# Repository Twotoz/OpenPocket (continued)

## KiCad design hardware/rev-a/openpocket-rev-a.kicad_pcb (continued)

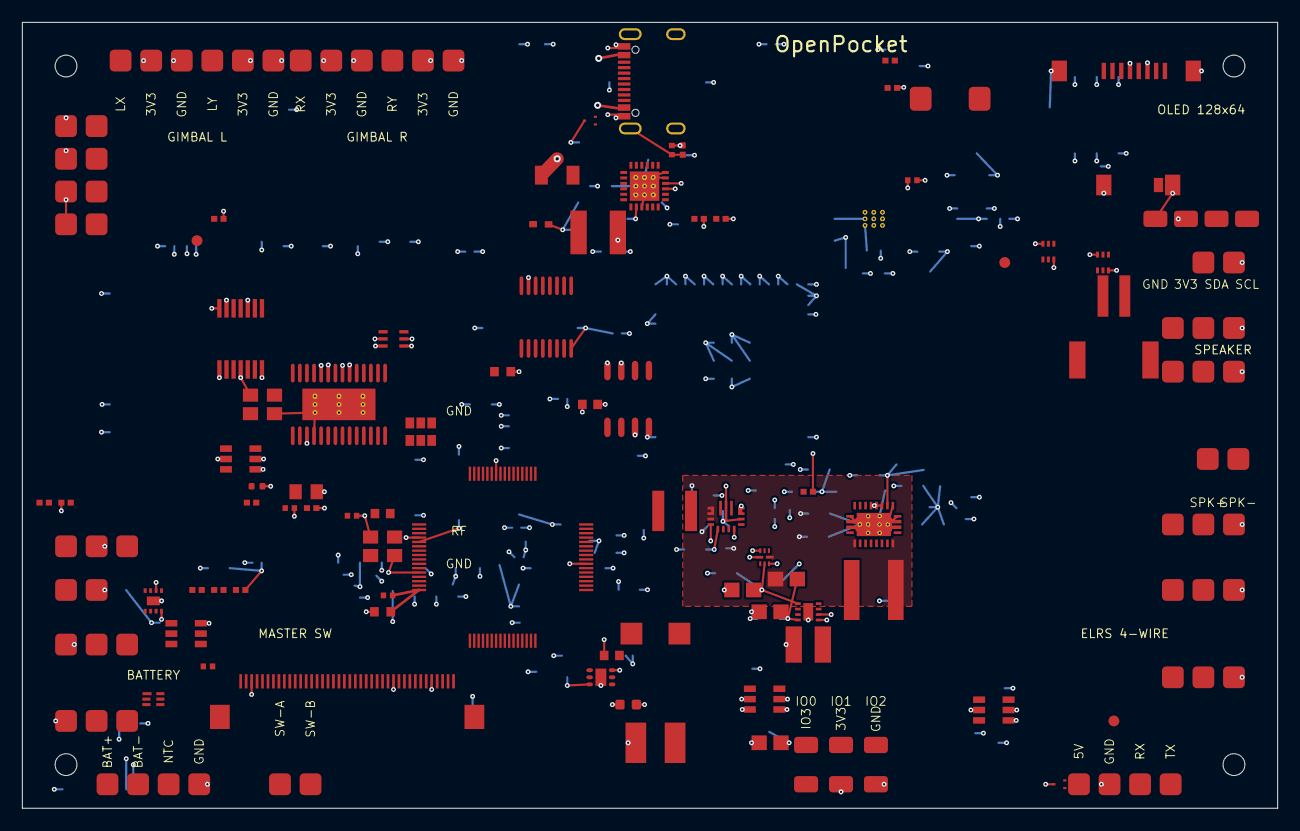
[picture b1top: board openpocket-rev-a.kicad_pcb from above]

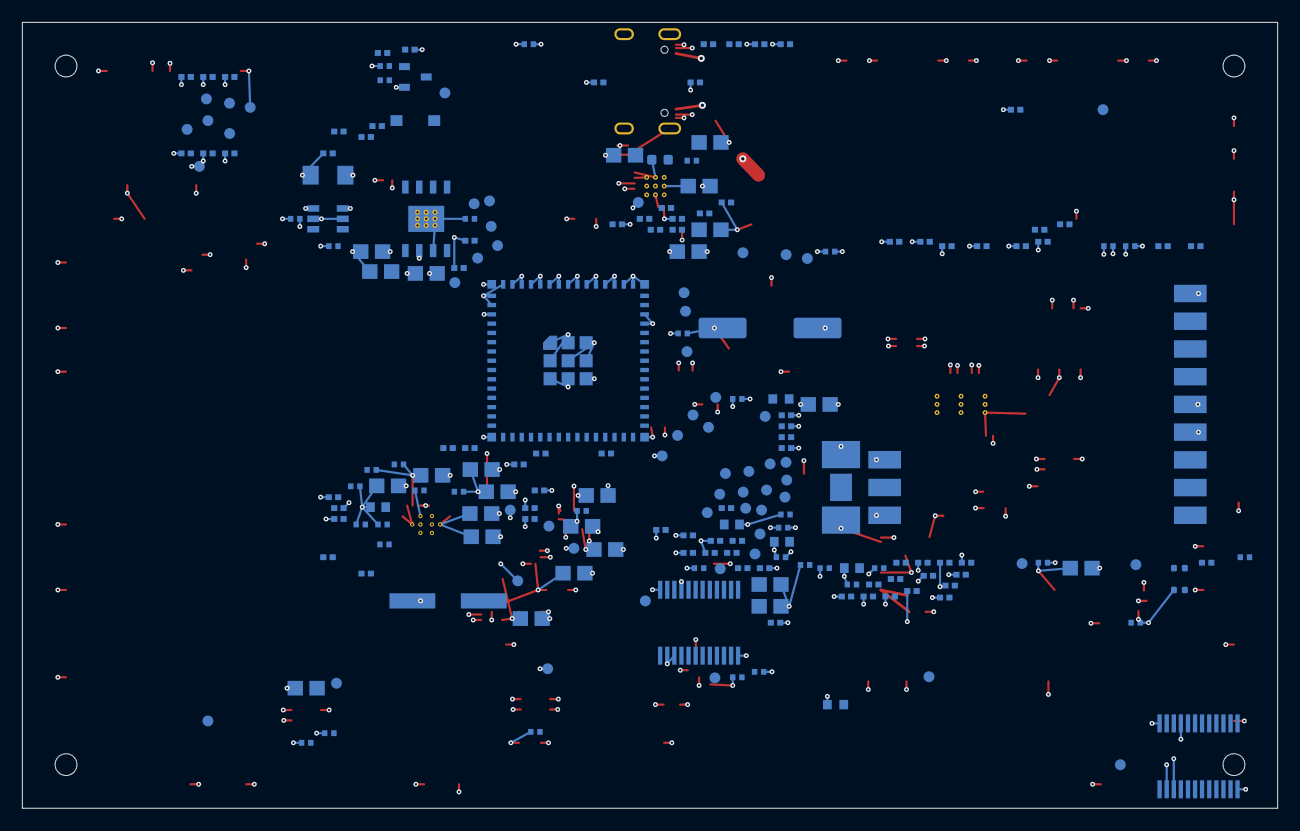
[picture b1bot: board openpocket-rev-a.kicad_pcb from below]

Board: 8 copper layers, 115.0 x 72.0 mm, 315 parts (220 on the bottom side), 235 nets.

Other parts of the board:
FID1, FID2, FID3, FID4, FID5, FID6: Fiducial_1mm_Mask2mm
MH1, MH2, MH3, MH4: MountingHole_2mm

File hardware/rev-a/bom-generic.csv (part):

Designator,Value,Manufacturer,MPN,LCSC,Package,Qty,DNP,Notes
U1,ESP32-S3-MINI-1U-N8,Espressif,ESP32-S3-MINI-1U-N8,C2980299,ESP32-S3-MINI-1U,1,no,
J2,USB-C,GCT,USB4105-GF-A,C3020560,USB4105-GF-A,1,no,
ESD1,USB ESD,Texas Instruments,TPD2EUSB30DRTR,C97502,SOT-9X3-3,1,no,
F1,USB VBUS resettable fuse,Littelfuse,1206L200PR,C151163,1206,1,no,
TVS1,USB VBUS TVS,onsemi,ESD5Z5.0T1G,C82044,SOD-523,1,no,
U2,1S charger/power path,Texas Instruments,BQ25895RTWR,C80200,WQFN-24-EP,1,no,
U3,1S protector,Texas Instruments,BQ29700DSER,C183096,WSON-6,1,no,
Q1,dual protection FET,FUXINSEMI,FS8205A,C908265,SOT-23-6,1,no,
U4,fuel gauge,Analog Devices,MAX17048G+T10,C2682616,TDFN-8-EP,1,no,
U20,master load switch,Texas Instruments,TPS22992SRXNR,C3229354,WQFN-8,1,no,
U5,3V3 buck-boost,Texas Instruments,TPS63070RNMR,C109322,VQFN-15,1,no,
U6,5V boost,Texas Instruments,TPS61088RHLR,C87357,VQFN-20-EP,1,no,
U7,5V_VIDEO load switch,Texas Instruments,TPS22918DBVR,C131941,SOT-23-6,1,no,
U8,5V_DISPLAY load switch,Texas Instruments,TPS22918DBVR,C131941,SOT-23-6,1,no,
U9,5V_ELRS load switch,Texas Instruments,TPS22918DBVR,C131941,SOT-23-6,1,no,
U10,display 3V3 buck,Texas Instruments,TPS62162DSGR,C40256,WSON-8-EP,1,no,
MOD1,RX5808 SPI receiver,WREKD,RX5808 SPI-modified,C2908157,SMD-12_23.0X28.0X2.54P,1,no,pre-order or consigned
U11,analog OSD,Zhongkewei,AT7456E,C82351,TSSOP-28-EP,1,no,
U12,OSD 3V3-to-5V,Texas Instruments,SN74AHCT125PWR,C36365,TSSOP-14,1,no,
U13,OSD 5V-to-3V3,Texas Instruments,SN74LVC1T45DCKR,C9382,SC70-6,1,no,
U14,CVBS TFT controller,Actions Microelectronics,AMT630A,C9900018923,LQFP-64_14x14_P0.4,1,no,
U15,AMT boot flash,Winbond,W25X05CLSNIG,C2641187,SOIC-8,1,no,
U16,AMT flash mux,Texas Instruments,SN74CB3Q3257PWR,C397142,TSSOP-16,1,no,
J1,ER-TFT050A3-2 FFC,Hirose,FH12-40S-0.5SH(55),C202114,FH12-40S-0.5SH(55),1,no,
U17,backlight boost,Texas Instruments,TPS61165DRVR,C122568,WSON-6-EP,1,no,
U18,GPIO expander 0x20,Texas Instruments,TCA9535PWR,C130204,TSSOP-24,1,no,
U19,GPIO expander 0x21,Texas Instruments,TCA9535PWR,C130204,TSSOP-24,1,no,
BZ1,passive magnetic buzzer,Fengming,YS-SBZ7525C05R30,C7421675,SMD-7.5x7.5,1,no,
Q2,Q_BUZZ buzzer MOSFET,Alpha & Omega,AO3400A,C20917,SOT-23,1,no,
D2,D_BUZZ buzzer flyback,LGE,1N4148W,C81598,SOD-123,1,no,
U21,I2S speaker amplifier,Nsiway,NS4168,C910588,ESOP-8-EP,1,no,
J4,speaker connector,JST,S2B-PH-SM4-TB(LF)(SN),C295747,JST-PH-2-SMD,1,no,
J13,speaker solder pads,OpenPocket,SOLDER-PADS-2,CONS,EDGE-PADS-2,1,yes,integral differential speaker pads; neither pad is ground
J14,SSD1306 128x64 OLED pads,OpenPocket,DEV-PADS-4,CONS,DEV-PADS-4,1,yes,four-wire SSD1306/SH1106 128x64 OLED; shared GPIO15/GPIO16 I2C bus
J15,expander developer pads,OpenPocket,DEV-PADS-6,CONS,DEV-PADS-6,1,yes,hand-solder TCA9535 U19 slow-I/O access
U22,3V3_SD load switch,Texas Instruments,TPS22918DBVR,C131941,SOT-23-6,1,no,
J12,push-push microSD,SOFNG,TF-001A-P3,C3021282,TF-001A-P3,1,no,card detect active-low; card ejects toward top edge
ESD2,microSD ESD array A,Texas Instruments,TPD4E001DRLR,C527516,SOT-563,1,no,
ESD3,microSD ESD array B,Texas Instruments,TPD4E001DRLR,C527516,SOT-563,1,no,
TP1,3V3_SD test pad,OpenPocket,PCB-TEST-PAD-1.0MM,N/A,TEST-PAD-1.0MM,1,yes,bare ENIG copper test feature; not an assembled component
TP2,SD_CLK test pad,OpenPocket,PCB-TEST-PAD-1.0MM,N/A,TEST-PAD-1.0MM,1,yes,bare ENIG copper test feature; not an assembled component
TP3,SD_CMD test pad,OpenPocket,PCB-TEST-PAD-1.0MM,N/A,TEST-PAD-1.0MM,1,yes,bare ENIG copper test feature; not an assembled component
TP4,SD_D0 test pad,OpenPocket,PCB-TEST-PAD-1.0MM,N/A,TEST-PAD-1.0MM,1,yes,bare ENIG copper test feature; not an assembled component
TP5,SD_CARD_DETECT test pad,OpenPocket,PCB-TEST-PAD-1.0MM,N/A,TEST-PAD-1.0MM,1,yes,bare ENIG copper test feature; not an assembled component
TP6,GND test pad,OpenPocket,PCB-TEST-PAD-1.0MM,N/A,TEST-PAD-1.0MM,1,yes,bare ENIG copper test feature; not an assembled component
J3,battery/NTC,OpenPocket,SOLDER-PADS-4,CONS,EDGE-PADS-4,1,yes,"integral solder pads; user-wired, not an assembly item"
J5,master switch,OpenPocket,SOLDER-PADS-2,CONS,EDGE-PADS-2,1,yes,"integral solder pads; user-wired, not an assembly item"
J6,ELRS,OpenPocket,SOLDER-PADS-4,CONS,EDGE-PADS-4,1,yes,four-wire ELRS UART/power pads; BOOT and RESET remain internal debug nets
ESD4,ELRS UART ESD,Texas Instruments,TPD2EUSB30DRTR,C97502,SOT-9X3-3,1,no,
J7,left gimbal,OpenPocket,SOLDER-PADS-6,CONS,EDGE-PADS-6,1,yes,"integral solder pads; user-wired, not an assembly item"
J8,right gimbal,OpenPocket,SOLDER-PADS-6,CONS,EDGE-PADS-6,1,yes,"integral solder pads; user-wired, not an assembly item"
J9,controls,OpenPocket,SOLDER-PADS-22,CONS,EDGE-PADS-22,1,yes,"integral solder pads; user-wired, not an assembly item"
J16,controls ground pads,OpenPocket,SOLDER-PADS-2,CONS,EDGE-PADS-2,1,yes,two shared ground returns for J9 buttons/switches
J11,5.8 GHz antenna U.FL,Hirose,U.FL-R-SMT-1(10),C88373,U.FL,1,no,populate on bottom; accepts U.FL/MHF1 plug vertically; secure cable to enclosure
R1,5.1k,Yageo,RC0402FR-075K1L,C105872,0402,1,no,
R2,5.1k,Yageo,RC0402FR-075K1L,C105872,0402,1,no,
R3,10k,Yageo,RC0402FR-0710KL,C60490,0402,1,no,
R4,10k,Yageo,RC0402FR-0710KL,C60490,0402,1,no,
R5,100k,Yageo,RC0402FR-07100KL,C60491,0402,1,no,
R6,100,Yageo,RC0402FR-07100RL,C106232,0402,1,no,
R7,100k,Yageo,RC0402FR-07100KL,C60491,0402,1,no,
R8,100k,Yageo,RC0402FR-07100KL,C60491,0402,1,no,
R9,4.99,Yageo,RC0603FR-074R99L,C137704,0402,1,no,
R10,18,Yageo,RC0603FR-0718RL,C245924,0402,1,no,
R11,56,Yageo,RC0603FR-0756RL,C126360,0402,1,no,
R12,100k,Yageo,RC0402FR-07100KL,C60491,0402,1,no,
R13,100k,Yageo,RC0402FR-07100KL,C60491,0402,1,no,
R14,2.2k,Yageo,RC0402FR-072K2L,C114762,0402,1,no,
R15,2.2k,Yageo,RC0402FR-072K2L,C114762,0402,1,no,
R16,100k,Yageo,RC0402FR-07100KL,C60491,0402,1,no,
R18,1M,Yageo,RC0402FR-071ML,C138033,0402,1,no,
R20,316k,Yageo,RC0402FR-07316KL,C185427,0402,1,no,
R21,100k,Yageo,RC0402FR-07100KL,C60491,0402,1,no,
R22,1M,Yageo,RC0402FR-071ML,C138033,0402,1,no,
R23,316k,Yageo,RC0402FR-07316KL,C185427,0402,1,no,
R24,150k,Yageo,RC0402FR-07150KL,C93947,0402,1,no,
R25,1k,Yageo,RC0402FR-071KL,C106235,0402,1,no,
R26,12k,Yageo,RC0402FR-0712KL,C114760,0402,1,no,
R27,18k,Yageo,RC0402FR-0718KL,C138044,0402,1,no,
R28,27,Yageo,RC0402FR-0727RL,C138021,0402,1,no,
R29,27,Yageo,RC0402FR-0727RL,C138021,0402,1,no,
R30,10k,Yageo,RC0402FR-0710KL,C60490,0402,1,no,
R31,10k,Yageo,RC0402FR-0710KL,C60490,0402,1,no,
R32,10k,Yageo,RC0402FR-0710KL,C60490,0402,1,no,
R33,10k,Yageo,RC0402FR-0710KL,C60490,0402,1,no,
R34,10k,Yageo,RC0402FR-0710KL,C60490,0402,1,no,
R35,10k,Yageo,RC0402FR-0710KL,C60490,0402,1,no,
R36,100k,Yageo,RC0402FR-07100KL,C60491,0402,1,no,
R37,27,Yageo,RC0402FR-0727RL,C138021,0402,1,no,
R38,27,Yageo,RC0402FR-0727RL,C138021,0402,1,no,
R39,27,Yageo,RC0402FR-0727RL,C138021,0402,1,no,
R40,100k,Yageo,RC0402FR-07100KL,C60491,0402,1,no,
R41,100k,Yageo,RC0402FR-07100KL,C60491,0402,1,no,
R42,750,Yageo,RC0402FR-07750RL,C137936,0402,1,no,
R43,10k,Yageo,RC0402FR-0710KL,C60490,0402,1,no,
R44,10k,Yageo,RC0402FR-0710KL,C60490,0402,1,no,
R45,10k,Yageo,RC0402FR-0710KL,C60490,0402,1,no,
R46,5.23k,Yageo,RC0402FR-075K23L,C477746,0402,1,no,
R47,30.1k,Yageo,RC0402FR-0730K1L,C138009,0402,1,no,
R48,10k,Yageo,RC0402FR-0710KL,C60490,0402,1,no,
R49,10k,Yageo,RC0402FR-0710KL,C60490,0402,1,no,
R50,10k,Yageo,RC0402FR-0710KL,C60490,0402,1,no,
R51,330k,Yageo,RC0402FR-07330KL,C138006,0402,1,no,
R52,18.2k,Yageo,RC0402FR-0718K2L,C274351,0402,1,no,
R53,1k,Yageo,RC0402FR-071KL,C106235,0402,1,no,
R54,1M,Yageo,RC0402FR-071ML,C138033,0402,1,no,
R55,10,Yageo,RC0402FR-0710RL,C138066,0402,1,no,
R56,330,Uniroyal Electronics,0402WGF3300TCE,C25104,0402,1,no,
R57,2.2k,Uniroyal Electronics,0402WGF2201TCE,C25879,0402,1,no,
R58,33,Yageo,RC0402FR-0733RL,C138002,0402,1,no,
R59,33,Yageo,RC0402FR-0733RL,C138002,0402,1,no,
R60,33,Yageo,RC0402FR-0733RL,C138002,0402,1,no,
R61,33,Yageo,RC0402FR-0733RL,C138002,0402,1,no,
R62,5.1M,Uniroyal Electronics,0402WGF5104TCE,C270595,0402,1,no,
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
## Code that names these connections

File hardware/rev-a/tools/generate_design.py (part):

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    ("PG","DISPLAY_3V3_PG"),("EP",G)],78,50)

# Video path and display controller.
rxpins=[("GND",G),("ANT","RX_RF"),("RF_GND",G),("DATA","RX_DATA"),
        ("LE","RX_LE"),("CLK","RX_CLK"),("DGND",G),("5V","5V_VIDEO_FILT"),
        ("RSSI","RX_RSSI_RAW"),("AUDIO","RX_AUDIO_TP"),("VIDEO","VRX_VIDEO_RAW"),
        ("AGND",G)]
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            "SD_CARD_DETECT", "EN_3V3_SD", "EN_5V_VIDEO",
            "EN_5V_DISPLAY", "EN_5V_ELRS", "LCD_DISP",
            "DEV_IO0", "DEV_IO1", "DEV_IO2", "DEV_IO3"]
    pins=[("INT","EXP_INT"),("A1",G),("A2",G)]
    pins += [(f"P0{i}",port_nets[i]) for i in range(8)]
    pins += [("GND",G)]
    pins += [(f"P1{i}",port_nets[i+8]) for i in range(8)]
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    "EDGE-PADS-2",[("SPK+","SPK+"),("SPK-","SPK-")],86,26,
    dnp=True,notes="integral differential speaker pads; neither pad is ground")
# Issue #4 developer access pads.  The OLED shares the existing ESP32 I2C
# bus; DEV_IO0..3 are the previously unused U19/TCA9535 port pins.
add("J14","SSD1306 128x64 OLED pads","OpenPocket","DEV-PADS-4","CONS",
    "DEV-PADS-4",[("GND","GND"),("VCC","3V3_LOGIC"),
                   ("SDA","I2C_SDA"),("SCL","I2C_SCL")],101,18,
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add("U22","3V3_SD load switch","Texas Instruments","TPS22918DBVR","C131941",
    "SOT-23-6",[("VIN","3V3_LOGIC"),("GND",G),("ON","EN_3V3_SD"),
    ("CT","3V3_SD_CT"),("QOD",G),("VOUT","3V3_SD")],24,8)
sd_socket_pins=[("DAT2","SD_DAT2"),("DAT3","SD_DAT3"),("CMD","SD_CMD"),
    ("VDD","3V3_SD"),("CLK","SD_CLK"),("VSS",G),("DAT0","SD_D0"),
    ("DAT1","SD_DAT1"),("CD","SD_CARD_DETECT")]+[("SH",G)]*4
add("J12","push-push microSD","SOFNG","TF-001A-P3","C3021282",
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        "U20": (29, 58, "F"),
        # Split the two high-current converter islands.  U5 belongs with the
        # 3V3 logic/battery side; U6 and L3 belong with the 5V boost output.
        # Keeping them in one horizontal row made SYS_SWITCHED and the 5V
        # switch node compete with the display/control fan-out.
        "U5": (64, 43, "F"),
        "U6": (78, 46, "F"), "U7": (20, 40, "F"),
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                pad_y_mm=f"{pcbnew.ToMM(position.y):.3f}",card_present_logic="n/a",
                source_evidence="SOFNG TF-001A-P3 drawing, vertical-view land pattern, P1-P8 at 0.80 mm pitch"))
        position=sd_pads["9"].GetPosition()
        w.writerow(dict(pin=9,function="CARD_DETECT",net="SD_CARD_DETECT",
            pad_x_mm=f"{pcbnew.ToMM(position.x):.3f}",
            pad_y_mm=f"{pcbnew.ToMM(position.y):.3f}",
            card_present_logic="low=fully inserted",
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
